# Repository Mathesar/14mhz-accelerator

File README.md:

# 14mhz-accelerator

This is 14MHz 68000 accelerator with 1MB fast ram and disable switch for the Amiga.
Tested on a rev. 5 Amiga 500. It might also work on other revisions and Amiga models but that has not been tested.
The design is licensed under CERN OHL-S V2.0

The design is a complete overhaul of a design by Livio Plos and Jorg Richter. Although based upon that design so much has been changed that it is almost like a new design.

Changes include:
* New clock doubler using an old school 4046 PLL to generate the 7MHz quadrature clock
This is more reliable than the RC delays in the original design. Alternatively the quadrature clock can
be taken from the motherboard. The latter has not been tested
* 3 input NOR's have been replaced by more common 2-input NOR's
In the process the basic design could be reduced to 4 IC's.
* some JK flipflops have been replaced by D latches.
* The E vs VMA/VPA timing has been improved for more robust write timing
* AS is now delayed before being fed to the motherboard fixing issues when the CPU does a chipset cycle after a CIA cycle.
* an optional 1Mb of zero waitstate Ranger RAM has been added to take full advantage of the 14MHz cpu.
* an optional reset timing based switch has been added to disable the ranger RAM upon boot.

## Variants
The accelerator can be build in 3 variant:
* Accelerator only
This only doubles the clock of the CPU to 14MHz. 
* Accelerator plus 1MB zero waitstate ranger RAM
The above but adds 1MB of fast RAM. This makes the accelerator about 2.7 times faster than a stock A500
* Accelerator plus 1MB zero waitstate ranger RAM plus disable circuit
The above but adds a timer based disable option for the RAM. By holdiing ctrl-amiga-amiga down for more 
than 5..6 seconds the RAM is disabled. It is enabled again on the next (less than 5..6 seconds) reset cycle

## Building hints
* use turned/machined pins only for the host connector!
The thick part is soldered on the accelerator, the thin part goes into the 68000 socket on the motherboard.
Makes sure to use the full length of the pins (only solder the tips in the accelerator board) so the accelerator sits above the Kickstart.
* an MC68HC000 (HCMOS version) is preferred as it uses less power and has better drive. This might also help with EPROM Kickstarts on a rev. 5 motherboard.
* The PLL might needs some tuning to provide a 50% dutycycle clock. 
Tuning is done by making the value of R3 slightly smaller or larger until testpoint J2 shows a nice
50% / 14MHZ clock signal. An oscilloscope works best here but alternatively a simple multimeter can be used to adjust the DC voltage
to read half the VCC value. (thus typically about 2.5V if VCC is **really** 5V)
* Alternatively the CDAC signal from the motherboard can be used. No tuning needed but untested at this point.

Here is a picture of the most basic variant (accelerator only) for reference purposes:

And here a picture of what a complete build should look like:

Have fun!

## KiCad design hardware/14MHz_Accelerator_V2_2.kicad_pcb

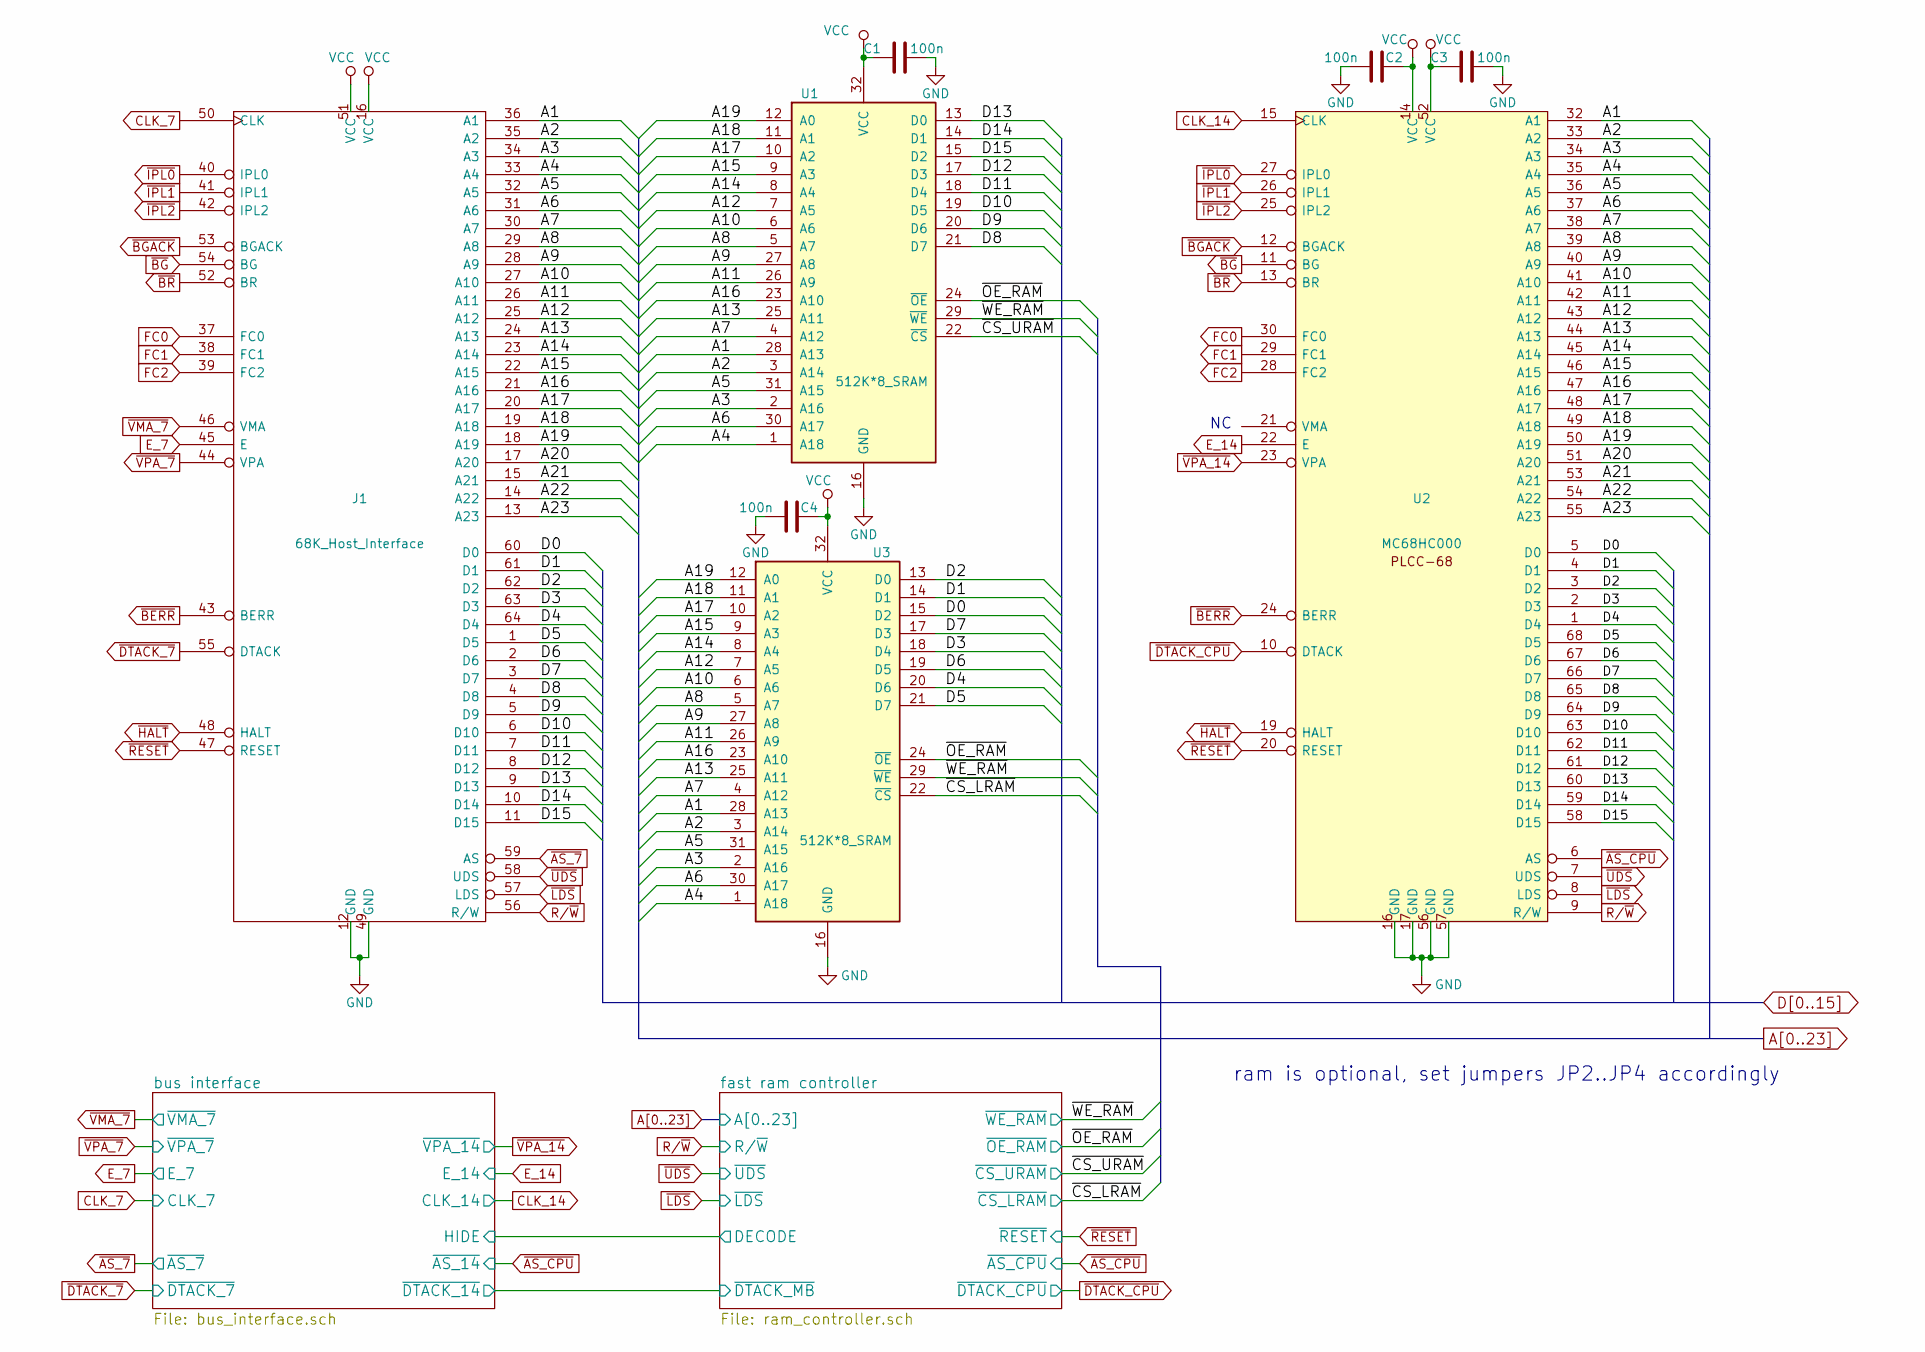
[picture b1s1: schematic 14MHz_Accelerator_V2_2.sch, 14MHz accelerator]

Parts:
C1, C2, C3, C4: 100n; C_0805_HandSoldering
J1: 68K_Host_Interface; DIP-64_W22.86mm
U1, U3: 512K*8_SRAM; TSOP-II-32_21.0x10.2mm_Pitch1.27mm
U2: MC68HC000; PLCC68_through_hole_socket

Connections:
/~CS_LRAM: U3.22 (~CS); also elsewhere on the board
/~CS_URAM: U1.22 (~CS); also elsewhere on the board
/~OE_RAM: U1.24 (~OE), U3.24 (~OE); also elsewhere on the board
/~WE_RAM: U1.29 (~WE), U3.29 (~WE); also elsewhere on the board
A1: J1.36 (A1), U1.28 (A13), U2.32 (A1), U3.28 (A13)
A2: J1.35 (A2), U1.3 (A14), U2.33 (A2), U3.3 (A14)
A3: J1.34 (A3), U1.2 (A16), U2.34 (A3), U3.2 (A16)
A4: J1.33 (A4), U1.1 (A18), U2.35 (A4), U3.1 (A18)
A5: J1.32 (A5), U1.31 (A15), U2.36 (A5), U3.31 (A15)
A6: J1.31 (A6), U1.30 (A17), U2.37 (A6), U3.30 (A17)
A7: J1.30 (A7), U1.4 (A12), U2.38 (A7), U3.4 (A12)
A8: J1.29 (A8), U1.5 (A7), U2.39 (A8), U3.5 (A7)
A9: J1.28 (A9), U1.27 (A8), U2.40 (A9), U3.27 (A8)
A10: J1.27 (A10), U1.6 (A6), U2.41 (A10), U3.6 (A6)
A11: J1.26 (A11), U1.26 (A9), U2.42 (A11), U3.26 (A9)
A12: J1.25 (A12), U1.7 (A5), U2.43 (A12), U3.7 (A5)
A13: J1.24 (A13), U1.25 (A11), U2.44 (A13), U3.25 (A11)
A14: J1.23 (A14), U1.8 (A4), U2.45 (A14), U3.8 (A4)
A15: J1.22 (A15), U1.9 (A3), U2.46 (A15), U3.9 (A3)
A16: J1.21 (A16), U1.23 (A10), U2.47 (A16), U3.23 (A10)
A17: J1.20 (A17), U1.10 (A2), U2.48 (A17), U3.10 (A2)
A18: J1.19 (A18), U1.11 (A1), U2.49 (A18), U3.11 (A1)
A19: J1.18 (A19), U1.12 (A0), U2.50 (A19), U3.12 (A0)
A20: J1.17 (A20), U2.51 (A20); also elsewhere on the board
A21: J1.15 (A21), U2.53 (A21); also elsewhere on the board
A22: J1.14 (A22), U2.54 (A22); also elsewhere on the board
A23: J1.13 (A23), U2.55 (A23); also elsewhere on the board
CLK_7: J1.50 (CLK); also elsewhere on the board
CLK_14: U2.15 (CLK); also elsewhere on the board
D0: J1.60 (D0), U2.5 (D0), U3.15 (D2)
D1: J1.61 (D1), U2.4 (D1), U3.14 (D1)
D2: J1.62 (D2), U2.3 (D2), U3.13 (D0)
D3: J1.63 (D3), U2.2 (D3), U3.18 (D4)
D4: J1.64 (D4), U2.1 (D4), U3.20 (D6)
D5: J1.1 (D5), U2.68 (D5), U3.21 (D7)
D6: J1.2 (D6), U2.67 (D6), U3.19 (D5)
D7: J1.3 (D7), U2.66 (D7), U3.17 (D3)
D8: J1.4 (D8), U1.21 (D7), U2.65 (D8)
D9: J1.5 (D9), U1.20 (D6), U2.64 (D9)
D10: J1.6 (D10), U1.19 (D5), U2.63 (D10)
D11: J1.7 (D11), U1.18 (D4), U2.62 (D11)
D12: J1.8 (D12), U1.17 (D3), U2.61 (D12)
D13: J1.9 (D13), U1.13 (D0), U2.60 (D13)
D14: J1.10 (D14), U1.14 (D1), U2.59 (D14)
D15: J1.11 (D15), U1.15 (D2), U2.58 (D15)
E_7: J1.45 (E); also elsewhere on the board
E_14: U2.22 (E); also elsewhere on the board
FC0: J1.37 (FC0), U2.30 (FC0)
FC1: J1.38 (FC1), U2.29 (FC1)
FC2: J1.39 (FC2), U2.28 (FC2)
GND: C1.2, C2.1, C3.2, C4.1, J1.12 (GND), J1.49 (GND), U1.16 (GND), U2.16 (GND), U2.17 (GND), U2.56 (GND), U2.57 (GND), U3.16 (GND); also elsewhere on the board
R/~W: J1.56 (R/W), U2.9 (R/W); also elsewhere on the board
VCC: C1.1, C2.2, C3.1, C4.2, J1.16 (VCC), J1.51 (VCC), U1.32 (VCC), U2.14 (VCC), U2.52 (VCC), U3.32 (VCC); also elsewhere on the board
~AS_7: J1.59 (AS); also elsewhere on the board
~AS_CPU: U2.6 (AS); also elsewhere on the board
~BERR~: J1.43 (BERR), U2.24 (BERR)
~BGACK~: J1.53 (BGACK), U2.12 (BGACK)
~BG~: J1.54 (BG), U2.11 (BG)
~BR~: J1.52 (BR), U2.13 (BR)
~DTACK_7: J1.55 (DTACK); also elsewhere on the board
~DTACK_CPU: U2.10 (DTACK); also elsewhere on the board
~HALT~: J1.48 (HALT), U2.19 (HALT)
~IPL0~: J1.40 (IPL0), U2.27 (IPL0)
~IPL1~: J1.41 (IPL1), U2.26 (IPL1)
~IPL2~: J1.42 (IPL2), U2.25 (IPL2)
~LDS: J1.57 (LDS), U2.8 (LDS); also elsewhere on the board
~RESET~: J1.47 (RESET), U2.20 (RESET); also elsewhere on the board
~UDS: J1.58 (UDS), U2.7 (UDS); also elsewhere on the board
~VMA_7: J1.46 (VMA), U2.23 (VPA); also elsewhere on the board
~VPA_7: J1.44 (VPA); also elsewhere on the board

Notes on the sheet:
ram is optional, set jumpers JP2..JP4 accordingly

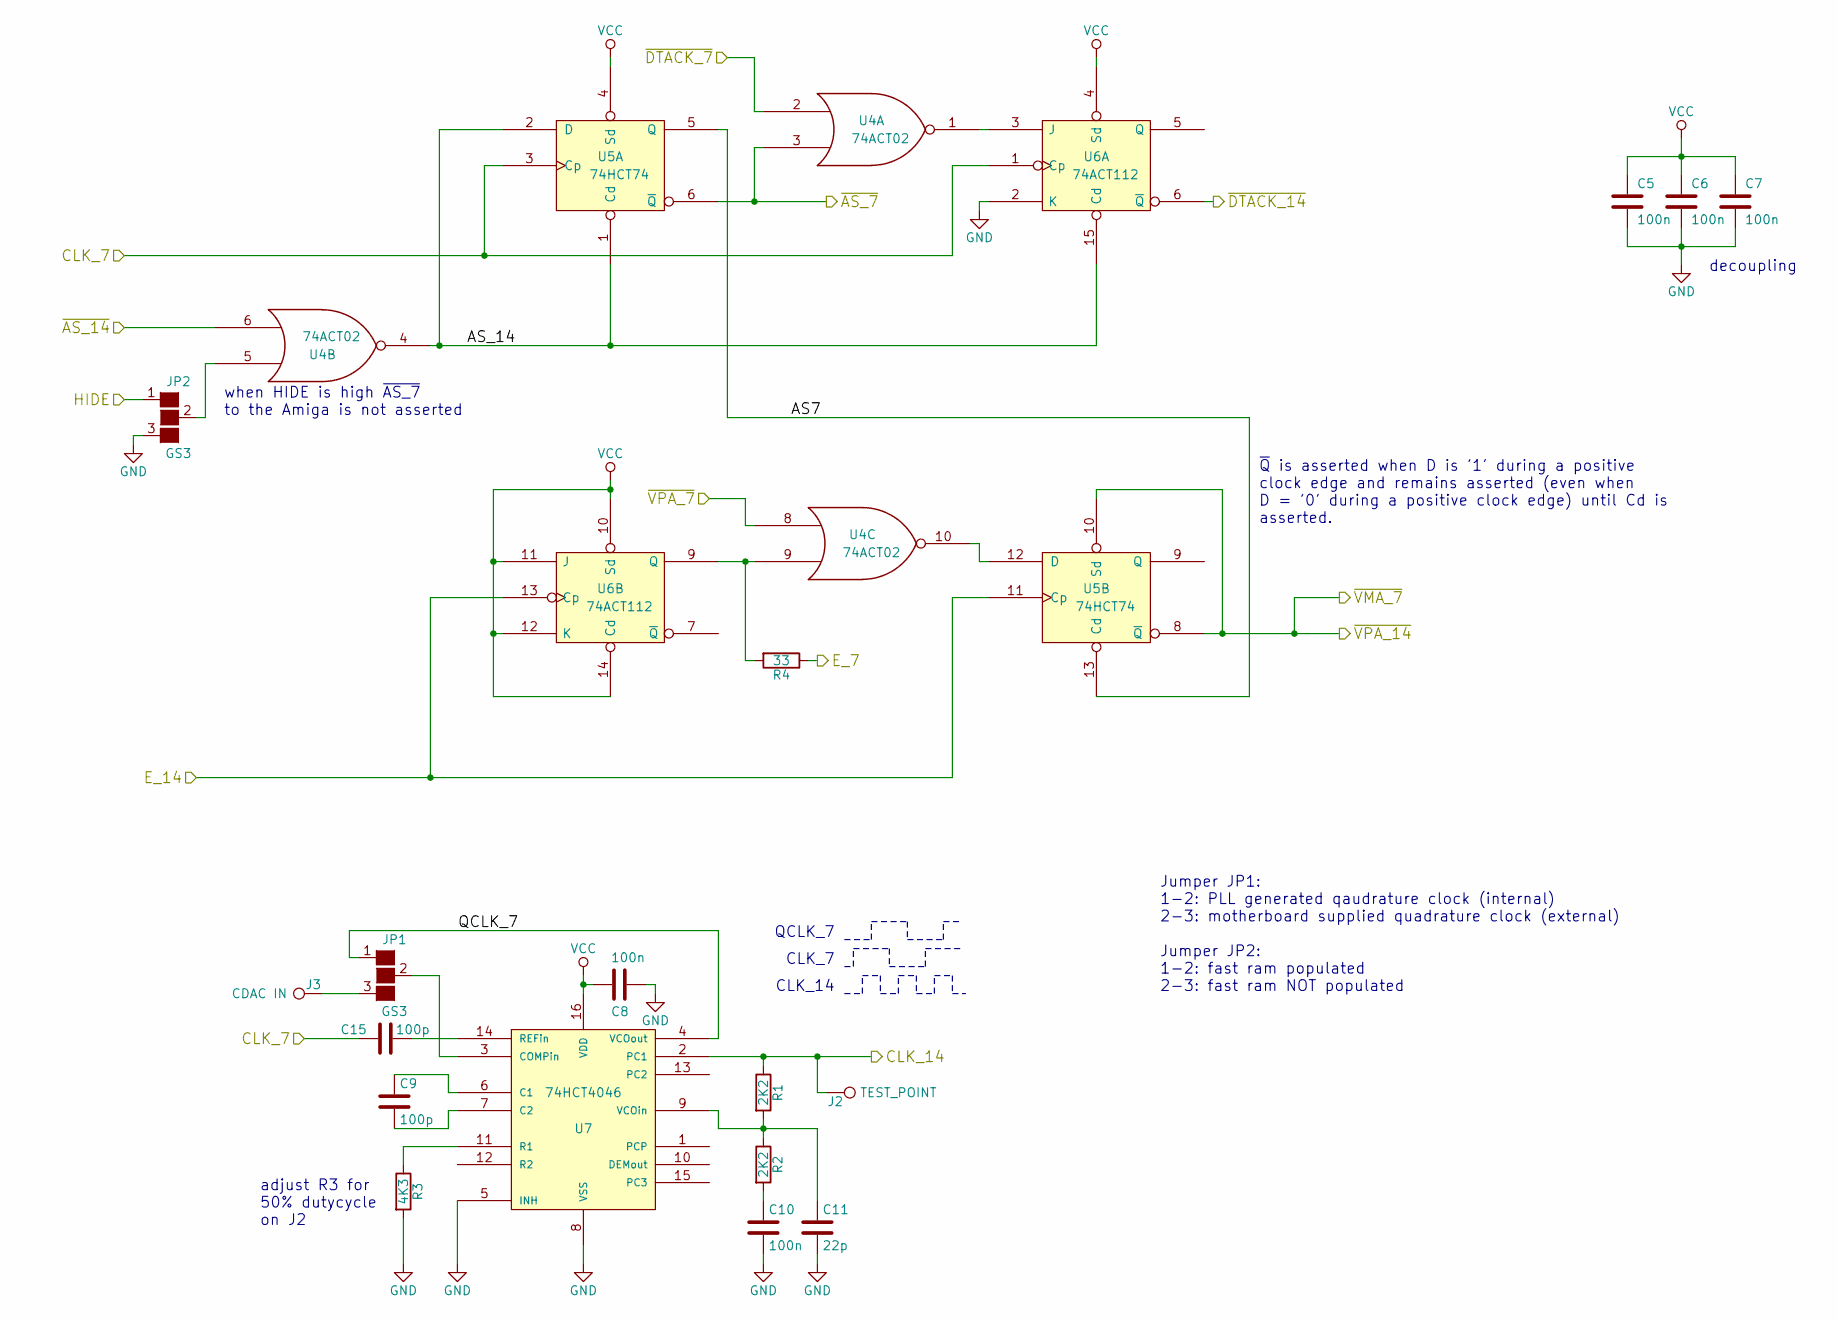
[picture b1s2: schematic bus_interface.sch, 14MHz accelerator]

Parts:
C5, C6, C7, C8, C10: 100n; C_0805_HandSoldering
C9, C15: 100p; C_0805_HandSoldering
C11: 22p; C_0805_HandSoldering
J2: TEST_POINT; PINTST
J3: CDAC IN; PINTST
JP1, JP2: GS3
R1, R2: 2K2; R_0805_HandSoldering
R3: 4K3; R_0805_HandSoldering
R4: 33; R_0805_HandSoldering
U4: 74ACT02; SOIC-14_3.9x8.7mm_Pitch1.27mm
U5: 74HCT74; SOIC-14_3.9x8.7mm_Pitch1.27mm
U6: 74ACT112; SOIC-16_3.9x9.9mm_Pitch1.27mm
U7: 74HCT4046; SOIC-16_3.9x9.9mm_Pitch1.27mm

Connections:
/bus interface/AS7: U5.5 (Q), U5.13 (Cd)
/bus interface/AS_14: U4.4, U5.1 (Cd), U5.2 (D), U6.15 (Cd)
/bus interface/QCLK_7: JP1.1 (G1), U7.4 (VCOout)
/bus interface/~DTACK_14: U6.6 (~Q); also elsewhere on the board
/fast ram controller/DECODE: JP2.1 (G1); also elsewhere on the board
CLK_7: C15.1, U5.3 (Cp), U6.1 (Cp); also elsewhere on the board
CLK_14: J2.1, R1.1, U7.2 (PC1); also elsewhere on the board
E_7: R4.1; also elsewhere on the board
E_14: U5.11 (Cp), U6.13 (Cp); also elsewhere on the board
GND: C5.2, C6.2, C7.2, C8.1, C10.2, C11.2, JP2.3 (G3), R3.2, U4.7 (GND), U5.7 (GND), U6.2 (K), U6.8 (GND), U7.5 (INH), U7.8 (VSS); also elsewhere on the board
unnamed: C9.1, U7.6 (C1)
unnamed: C9.2, U7.7 (C2)
unnamed: C10.1, R2.2
unnamed: C11.1, R1.2, R2.1, U7.9 (VCOin)
unnamed: C15.2, U7.14 (REFin)
unnamed: J3.1, JP1.3 (G3)
unnamed: JP1.2 (G2), U7.3 (COMPin)
unnamed: JP2.2 (G2), U4.5
unnamed: R3.1, U7.11 (R1)
unnamed: R4.2, U4.9, U6.9 (Q)
unnamed: U4.1, U6.3 (J)
unnamed: U4.10, U5.12 (D)
VCC: C5.1, C6.1, C7.1, C8.2, U4.14 (VCC), U5.4 (Sd), U5.14 (VCC), U6.4 (Sd), U6.10 (Sd), U6.11 (J), U6.12 (K), U6.14 (Cd), U6.16 (VCC), U7.16 (VDD); also elsewhere on the board
~AS_7: U4.3, U5.6 (~Q); also elsewhere on the board
~AS_CPU: U4.6; also elsewhere on the board
~DTACK_7: U4.2; also elsewhere on the board
~VMA_7: U5.8 (~Q), U5.10 (Sd); also elsewhere on the board
~VPA_7: U4.8; also elsewhere on the board

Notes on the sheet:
CLK_7
CLK_14
decoupling
QCLK_7
adjust R3 for 50% dutycycle on J2
when HIDE is high ~AS_7~ to the Amiga is not asserted
Jumper JP1: 1-2: PLL generated qaudrature clock (internal) 2-3: motherboard supplied quadrature clock (external) Jumper JP2: 1-2: fast ram populated 2-3: fast ram NOT populated
~Q~ is asserted when D is '1' during a positive clock edge and remains asserted (even when D = '0' during a positive clock edge) until Cd is asserted.

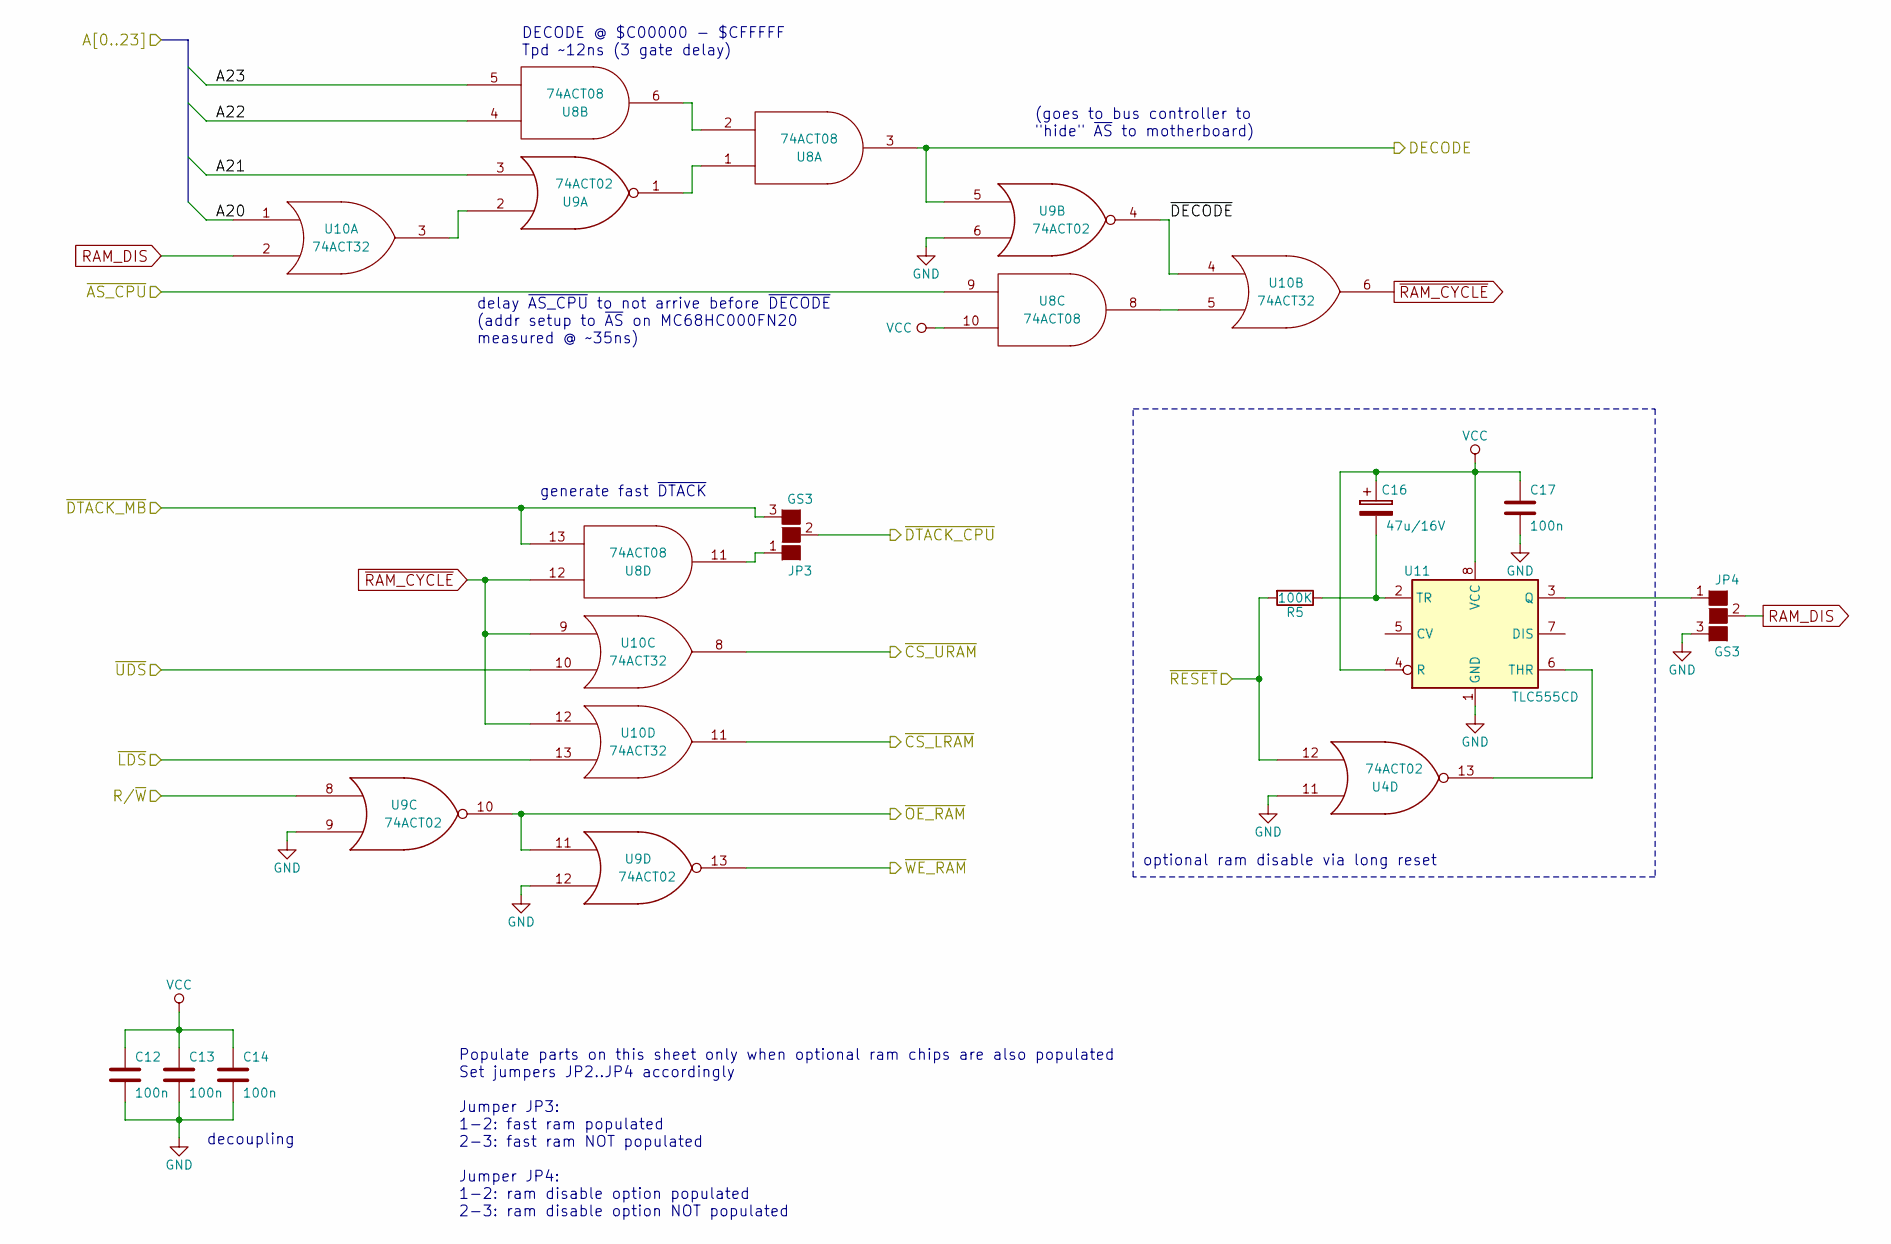
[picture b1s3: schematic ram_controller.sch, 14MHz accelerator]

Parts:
C12, C13, C14, C17: 100n; C_0805_HandSoldering
C16: 47u/16V; CP_Radial_D6.3mm_P2.50mm
JP3, JP4: GS3
R5: 100K; R_0805_HandSoldering
U4, U9: 74ACT02; SOIC-14_3.9x8.7mm_Pitch1.27mm
U8: 74ACT08; SOIC-14_3.9x8.7mm_Pitch1.27mm
U10: 74ACT32; SOIC-14_3.9x8.7mm_Pitch1.27mm
U11: TLC555CD; SOIC-8_3.9x4.9mm_Pitch1.27mm

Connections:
/bus interface/~DTACK_14: JP3.3 (G3), U8.13; also elsewhere on the board
/fast ram controller/DECODE: U8.3, U9.5; also elsewhere on the board
/fast ram controller/~DECODE: U9.4, U10.4
/~CS_LRAM: U10.11; also elsewhere on the board
/~CS_URAM: U10.8; also elsewhere on the board
/~OE_RAM: U9.10, U9.11; also elsewhere on the board
/~WE_RAM: U9.13; also elsewhere on the board
A20: U10.1; also elsewhere on the board
A21: U9.3; also elsewhere on the board
A22: U8.4; also elsewhere on the board
A23: U8.5; also elsewhere on the board
GND: C12.2, C13.2, C14.2, C17.2, JP4.3 (G3), U4.7 (GND), U4.11, U8.7 (GND), U9.6, U9.7 (GND), U9.9, U9.12, U10.7 (GND), U11.1 (GND); also elsewhere on the board
unnamed: C16.2, R5.1, U11.2 (TR)
unnamed: JP3.1 (G1), U8.11
unnamed: JP4.1 (G1), U11.3 (Q)
unnamed: U8.1, U9.1
unnamed: U8.2, U8.6
unnamed: U9.2, U10.3
unnamed: U8.8, U10.5
unnamed: U4.13, U11.6 (THR)
R/~W: U9.8; also elsewhere on the board
RAM_DIS: JP4.2 (G2), U10.2
VCC: C12.1, C13.1, C14.1, C16.1, C17.1, U4.14 (VCC), U8.10, U8.14 (VCC), U9.14 (VCC), U10.14 (VCC), U11.4 (R), U11.8 (VCC); also elsewhere on the board
~AS_CPU: U8.9; also elsewhere on the board
~DTACK_CPU: JP3.2 (G2); also elsewhere on the board
~LDS: U10.13; also elsewhere on the board
~RAM_CYCLE: U8.12, U10.6, U10.9, U10.12
~RESET~: R5.2, U4.12; also elsewhere on the board
~UDS: U10.10; also elsewhere on the board

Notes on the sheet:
DECODE @ $C00000 - $CFFFFF Tpd ~~12ns (3 gate delay)
delay ~AS_CPU~ to not arrive before ~DECODE~ (addr setup to ~AS~ on MC68HC000FN20 measured @ ~~35ns)
decoupling
optional ram disable via long reset
(goes to bus controller to "hide" ~AS~ to motherboard)
generate fast ~DTACK~
Populate parts on this sheet only when optional ram chips are also populated Set jumpers JP2..JP4 accordingly Jumper JP3: 1-2: fast ram populated 2-3: fast ram NOT populated Jumper JP4: 1-2: ram disable option populated 2-3: ram disable option NOT populated

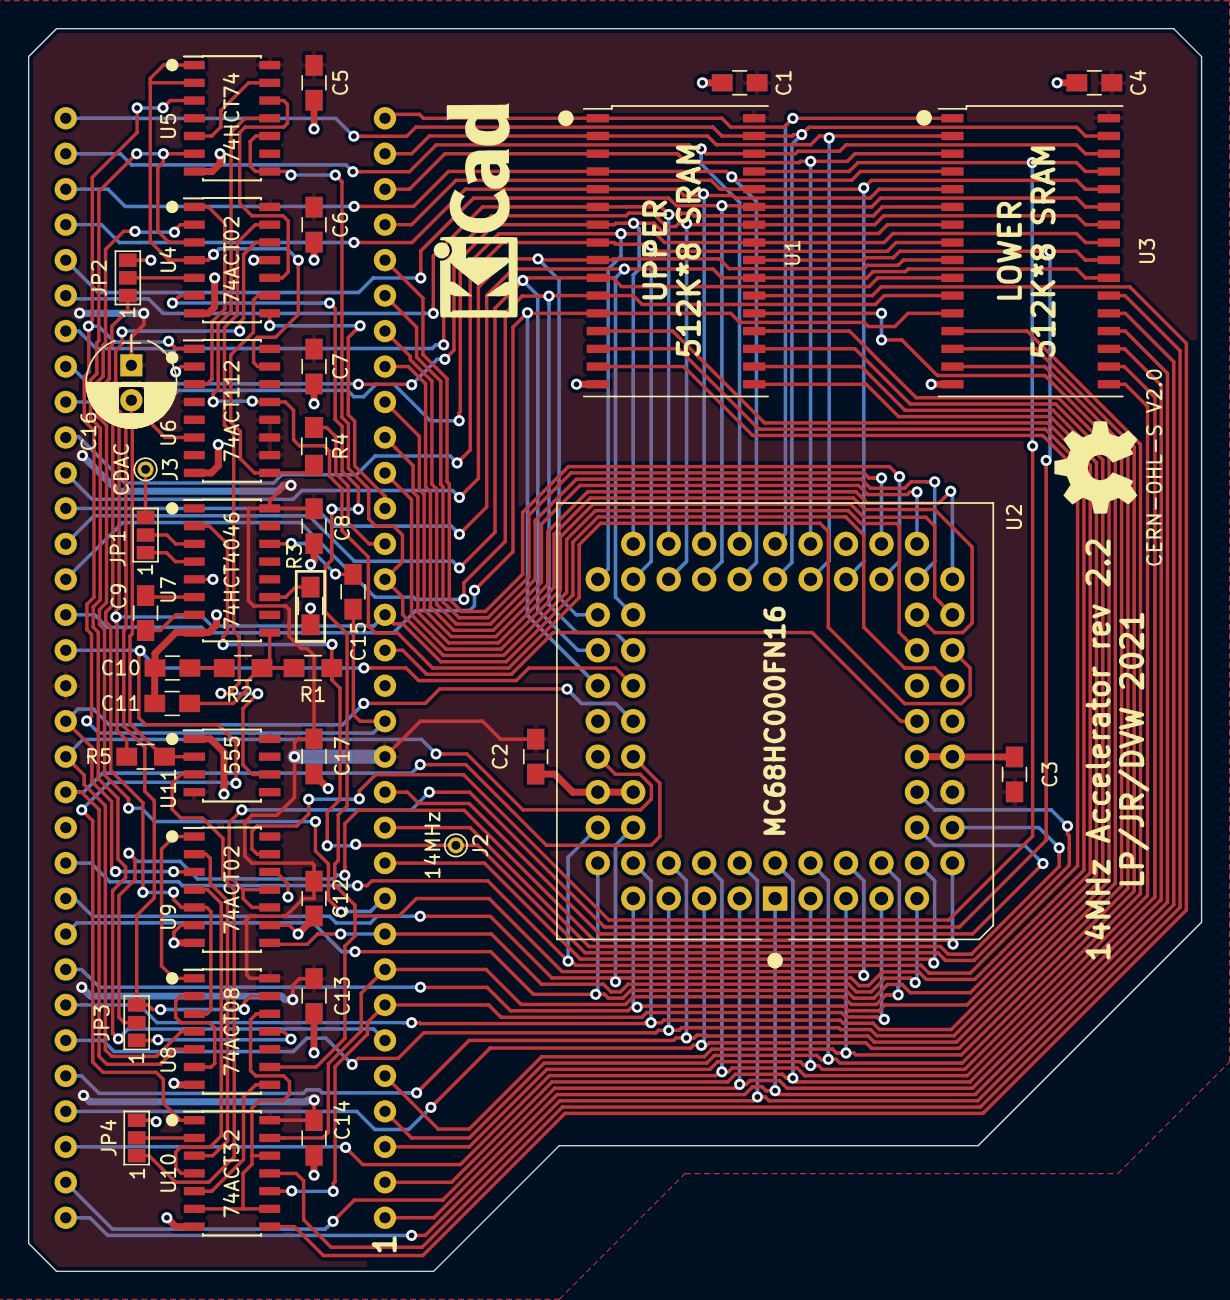
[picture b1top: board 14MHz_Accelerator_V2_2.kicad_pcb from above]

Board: 2 copper layers, 84.0 x 89.0 mm, 40 parts (1 on the bottom side), 98 nets.

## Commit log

2021-06-30 Added KiCad files
2021-07-03 minor layout optimizations
    added bill of materials
    added pictures
2021-07-03 Added license
    Added schematics in PDF format
2021-07-03 Typos fixed
2021-07-04 Add files via upload
    Added sysinfo and busspeed tests
2021-08-01 added remark that SRAM must be a 5V type
